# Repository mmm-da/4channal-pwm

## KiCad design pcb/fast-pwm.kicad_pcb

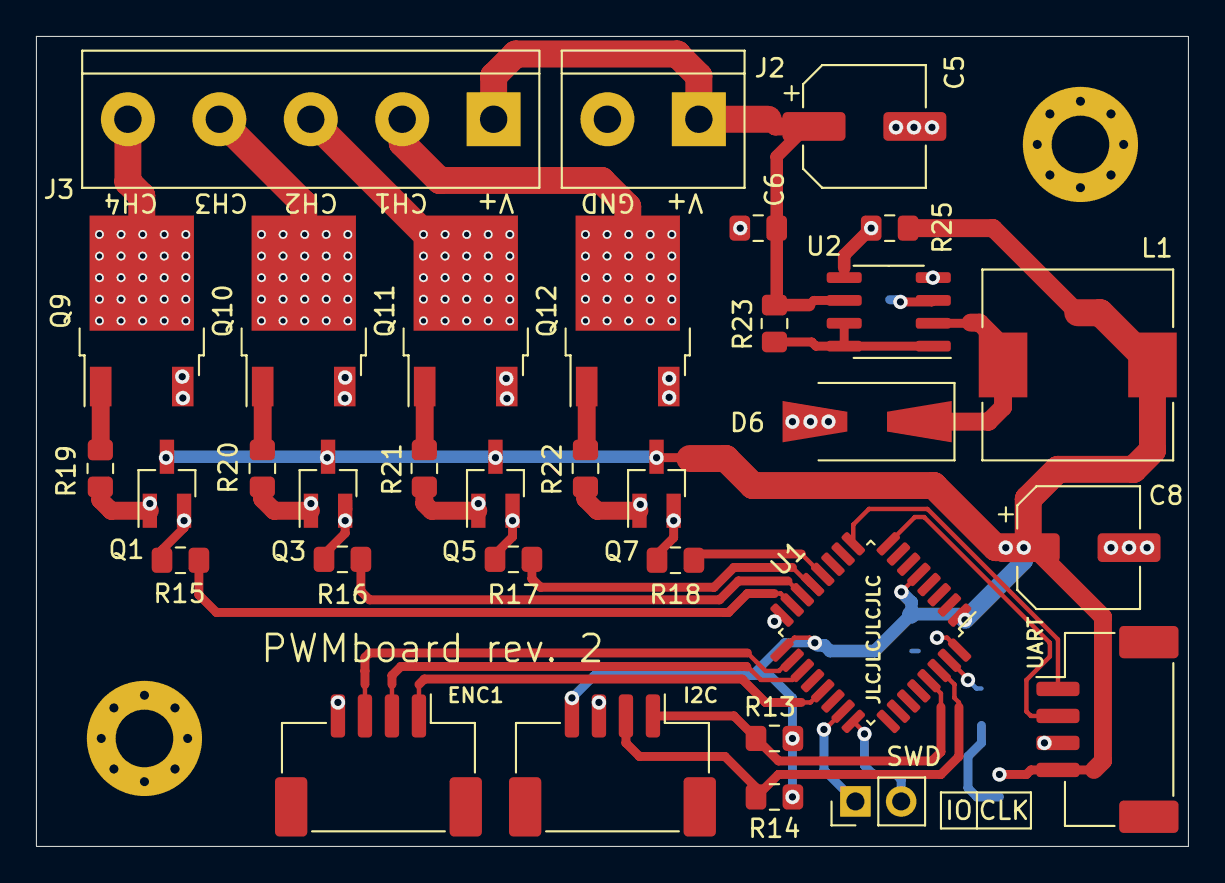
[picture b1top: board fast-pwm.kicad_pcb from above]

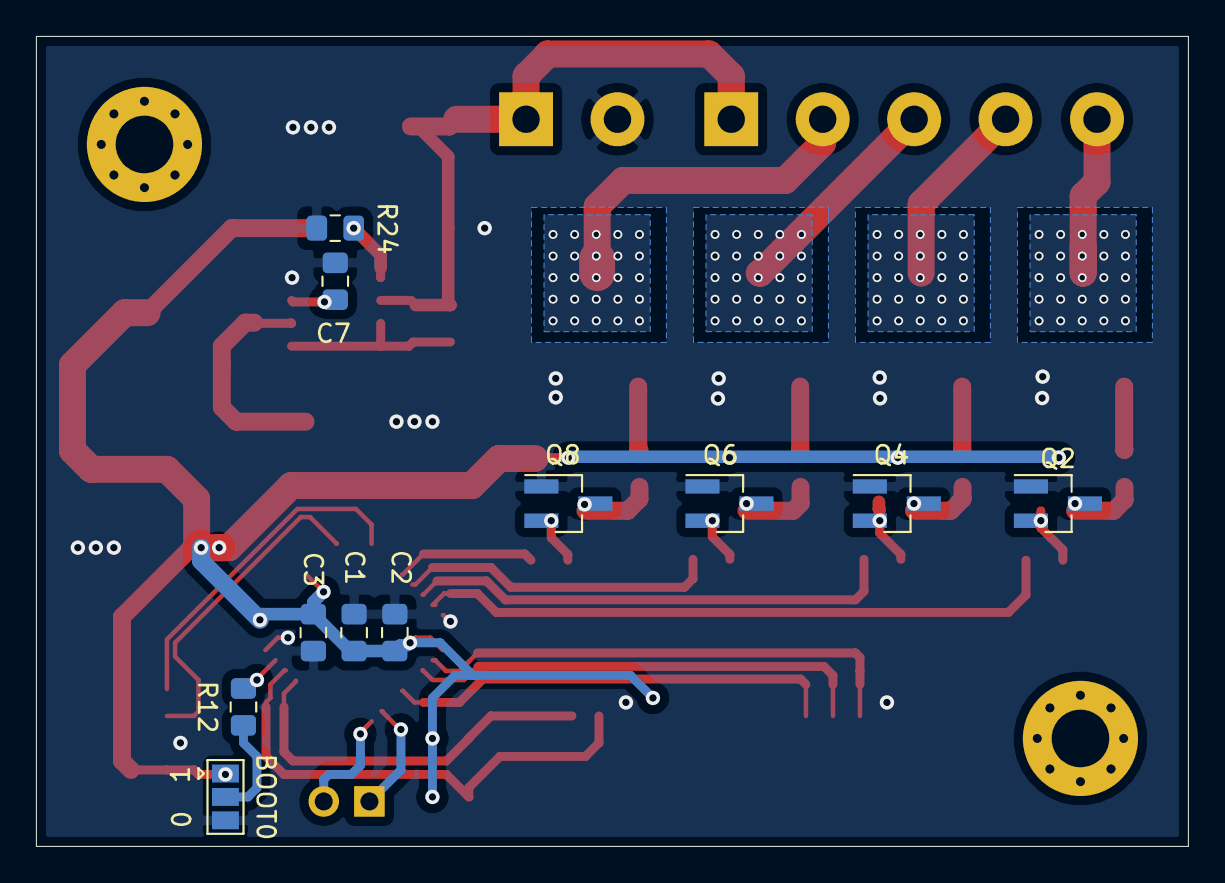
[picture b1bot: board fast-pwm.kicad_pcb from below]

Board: 2 copper layers, 64.0 x 45.0 mm, 44 parts (11 on the bottom side), 38 nets.

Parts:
BOOT0: Jumper_3_Open; SolderJumper-3_P1.3mm_Open_Pad1.0x1.5mm
C1: 1 uF; C_0805_2012Metric_Pad1.15x1.40mm_HandSolder
C2, C3, C6: 100 nF; C_0805_2012Metric_Pad1.15x1.40mm_HandSolder
C5: 100 uF; CP_Elec_6.3x5.4
C7: 270 pF; C_0805_2012Metric_Pad1.15x1.40mm_HandSolder
C8: 220 uF; CP_Elec_6.3x5.4
D6: 1N5819; D_SMA-SMB_Universal_Handsoldering
ENC1: ENC1; JST_ZE_BM04B-ZESS-TBT_1x04-1MP_P1.50mm_Vertical
I2C: UART; JST_ZE_BM04B-ZESS-TBT_1x04-1MP_P1.50mm_Vertical
J2: Клемма питания; TerminalBlock_bornier-2_P5.08mm
J3: Выходная клемма; TerminalBlock_bornier-5_P5.08mm
L1: 47 uH; L_10.4x10.4_H4.8
Q1, Q3, Q5, Q7: 2N3904; SOT-23_Handsoldering
Q2, Q4, Q6, Q8: 2N3905; SOT-23_Handsoldering
Q9, Q10, Q11, Q12: AOD4184A; TO-252-2
R12: 10k; R_0805_2012Metric_Pad1.15x1.40mm_HandSolder
R13, R14: 1k; R_0805_2012Metric_Pad1.15x1.40mm_HandSolder
R15, R16, R17, R18: 10 Omh; R_0805_2012Metric_Pad1.15x1.40mm_HandSolder
R19, R20, R21, R22: 11 Omh; R_0805_2012Metric_Pad1.15x1.40mm_HandSolder
R23: 0.3 Omh; R_0805_2012Metric_Pad1.15x1.40mm_HandSolder
R24: 11k; R_0805_2012Metric_Pad1.15x1.40mm_HandSolder
R25: 18k; R_0805_2012Metric_Pad1.15x1.40mm_HandSolder
SWD: SWD; PinHeader_1x02_P2.54mm_Vertical
U1: STM32F030K6Tx; LQFP-32_7x7mm_P0.8mm
U2: MC33063AD; SOIC-8_3.9x4.9mm_P1.27mm
UART: I2C; JST_ZE_BM04B-ZESS-TBT_1x04-1MP_P1.50mm_Vertical

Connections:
+12V: C5.1, C6.1, J2.1, J3.1, R23.2, U2.6
BOOT0: R12.2, U1.31
BUTTON1_EXT_IRQ: ENC1.1, U1.21
CH1: J3.2, Q12.2
CH2: J3.3, Q11.2
CH3: J3.4, Q10.2
CH4: J3.5, Q9.2
ENC1: ENC1.3, U1.18
ENC2: ENC1.2, U1.19
I2C_CLK: I2C.2, R14.1, U1.30
I2C_SDA: I2C.1, R13.1, U1.29
unnamed: C7.1, U2.3
unnamed: D6.1, L1.1, U2.2
unnamed: BOOT0.2, R12.1
unnamed: Q1.1, Q2.3, R19.2
unnamed: Q1.2, Q2.2, R15.1
unnamed: Q3.1, Q4.3, R20.2
unnamed: Q3.2, Q4.2, R16.1
unnamed: Q5.1, Q6.3, R21.2
unnamed: Q5.2, Q6.2, R17.1
unnamed: Q7.1, Q8.3, R22.2
unnamed: Q7.2, Q8.2, R18.1
unnamed: Q9.1, R19.1
unnamed: Q10.1, R20.1
unnamed: Q11.1, R21.1
unnamed: Q12.1, R22.1
unnamed: R23.1, U2.1, U2.7, U2.8
unnamed: R24.2, R25.2, U2.5
PWM_CH1: R18.2, U1.12
PWM_CH2: R17.2, U1.13
PWM_CH3: R16.2, U1.14
PWM_CH4: R15.2, U1.15
SWCLK: SWD.2, U1.24
SWDIO: SWD.1, U1.23
UART_RX: U1.9, UART.1
UART_TX: U1.8, UART.2
VDD: BOOT0.1, C1.1, C2.1, C3.1, C8.1, I2C.4, L1.2, Q1.3, Q3.3, Q5.3, Q7.3, R13.2, R14.2, R25.1, U1.1, U1.5, U1.17, UART.4
VSS: BOOT0.3, C1.2, C2.2, C3.2, C5.2, C6.2, C7.2, C8.2, D6.2, ENC1.4, I2C.3, J2.2, Q2.1, Q4.1, Q6.1, Q8.1, Q9.3, Q10.3, Q11.3, Q12.3, R24.1, U1.16, U1.32, U2.4, UART.3

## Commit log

2020-11-12 версия 0.2
    Надо сделать:
    - штуки под транзисторами
    - поправить ширину дорожек
    - попытатся укоротить плату на 1 см
    - разобратся с гребенкой
    - шелкография
2020-11-15 версия 0.3
2021-04-10 исправление ошибки на шелке
2021-04-10 исправление ошибки на шелке (BOM)
2021-04-10 изменил ревизию платы
2021-04-12 изменил номер ревизии
2021-04-12 вычищенный каркас без rtos
